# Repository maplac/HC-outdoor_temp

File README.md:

# HC-outdoor_temp

Nahrání bootloaderu do mikrokontroléru:
1. Do Arduino UNO nahrát ArduinoISP sketch.
2. Signálové a napájecí vodiče propojit, jak je uvedeno v https://www.arduino.cc/en/Tutorial/ArduinoToBreadboard a https://github.com/maplac/HC-outdoor_temp/blob/master/bootloader_connection.jpg.
3. Do Arduino IDE přidat MiniCore https://github.com/MCUdude/MiniCore.
4. Nastavit MiniCore - Board:Atmega328, Bootloader:yes, Variant:328P/328PA, BOD:1,8v, Clock:1 MHz internal, Compiler LTO:Disabled. https://github.com/maplac/HC-outdoor_temp/blob/master/bootloader_ide_settings.jpg
5. Nastavit programátor na "Arduino as ISP" a spustit Burn Bootloader.

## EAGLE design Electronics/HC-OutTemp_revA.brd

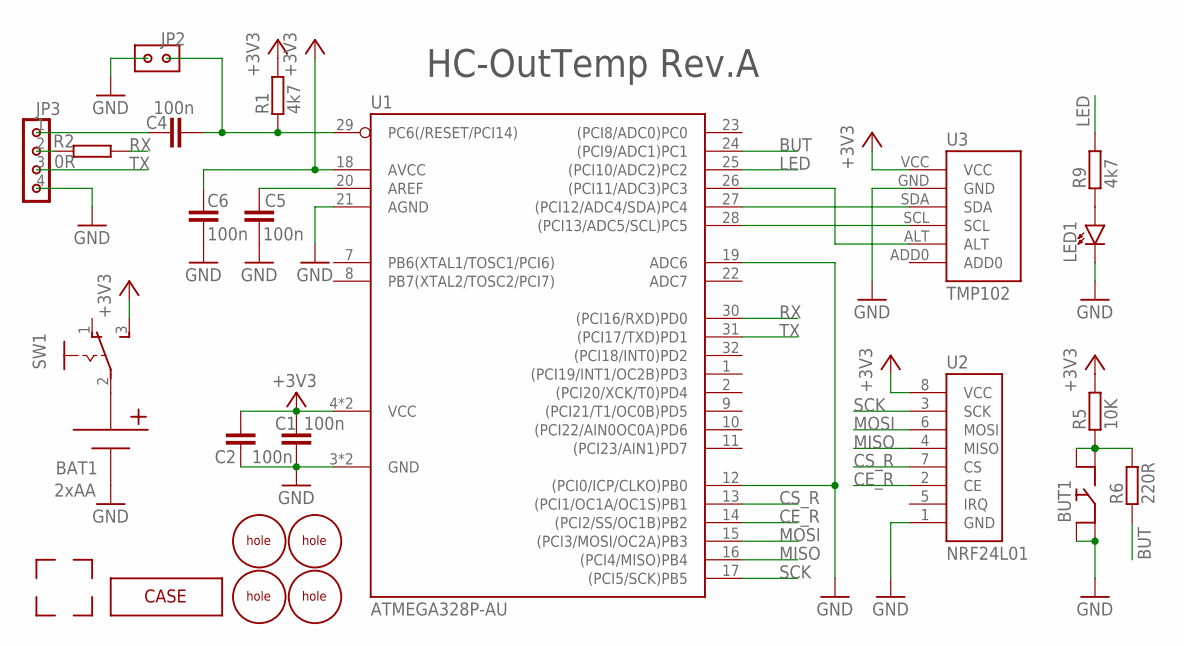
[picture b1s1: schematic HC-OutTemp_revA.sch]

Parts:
BAT1: 2xAA; 2XAA_BATTERY_HOLDER
BUT1: BUTTON'THT'; BUTTON
C1, C2, C4, C5, C6: 100n; C0805
JP2: PINHD2X1; PINHD-2X1
JP3: PINHD3X1; PINHD-4X1-90
LED1: LED'3MM'; LED3MM
R1, R9: 4k7; R0805
R2: 0R; R0805
R5: 10K; R0805
R6: 220R; R0805
SW1: SWITCH_SLIDE; SLIDE_SWITCH
U1: ATMEGA328P-AU; QFP80P900X900X120-32N
U2: NRF24L01
U3: TMP102
U$1, U$2, U$3, U$4: CORNER
U$5, U$6, U$7, U$8: HOLE
U$9: CASE'120X80X40'; CASE-120X80X40

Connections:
+3V3: C1.2, C2.2, C6.2, R1.2, R5.2, SW1.3 (S), U1.4 (VCC), U1.6 (VCC), U1.18 (AVCC), U2.8 (VCC), U3.VCC
BUT: R6.1, U1.24 ((PCI9/ADC1)PC1)
CE_R: U1.14 ((PCI2/SS/OC1B)PB2), U2.2 (CE)
CS_R: U1.13 ((PCI1/OC1A/OC1S)PB1), U2.7 (CS)
GND: BAT1.N, BUT1.2, BUT1.4, C1.1, C2.1, C5.2, C6.1, JP2.1, JP3.4, LED1.K, U1.3 (GND), U1.5 (GND), U1.12 ((PCI0/ICP/CLKO)PB0), U1.19 (ADC6), U1.21 (AGND), U2.1 (GND), U3.GND
LED: R9.2, U1.25 ((PCI10/ADC2)PC2)
MISO: U1.16 ((PCI4/MISO)PB4), U2.4 (MISO)
MOSI: U1.15 ((PCI3/MOSI/OC2A)PB3), U2.6 (MOSI)
unnamed: BAT1.P, SW1.2 (MIDDLE)
unnamed: C4.1, JP2.2, R1.1, U1.29 (PC6(/RESET/PCI14))
unnamed: LED1.A, R9.1
unnamed: U1.26 ((PCI11/ADC3)PC3), U3.ALT
unnamed: C5.1, U1.20 (AREF)
unnamed: C4.2, JP3.1
unnamed: BUT1.1, BUT1.3, R5.1, R6.2
unnamed: JP3.2, R2.2
unnamed: U1.27 ((PCI12/ADC4/SDA)PC4), U3.SDA
unnamed: U1.28 ((PCI13/ADC5/SCL)PC5), U3.SCL
RX: R2.1, U1.30 ((PCI16/RXD)PD0)
SCK: U1.17 ((PCI5/SCK)PB5), U2.3 (SCK)
TX: JP3.3, U1.31 ((PCI17/TXD)PD1)

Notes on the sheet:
HC-OutTemp Rev.A

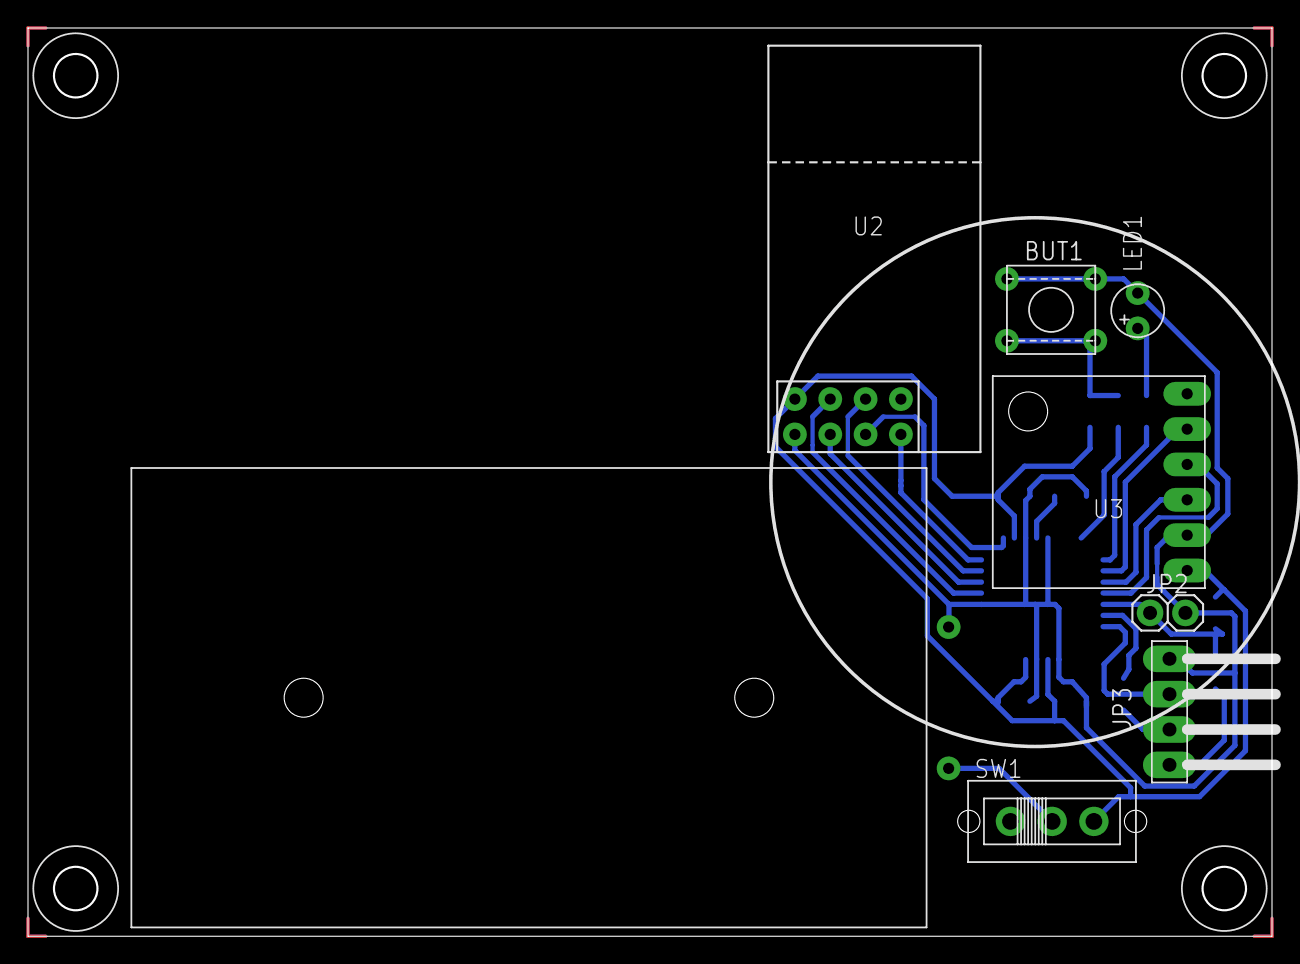
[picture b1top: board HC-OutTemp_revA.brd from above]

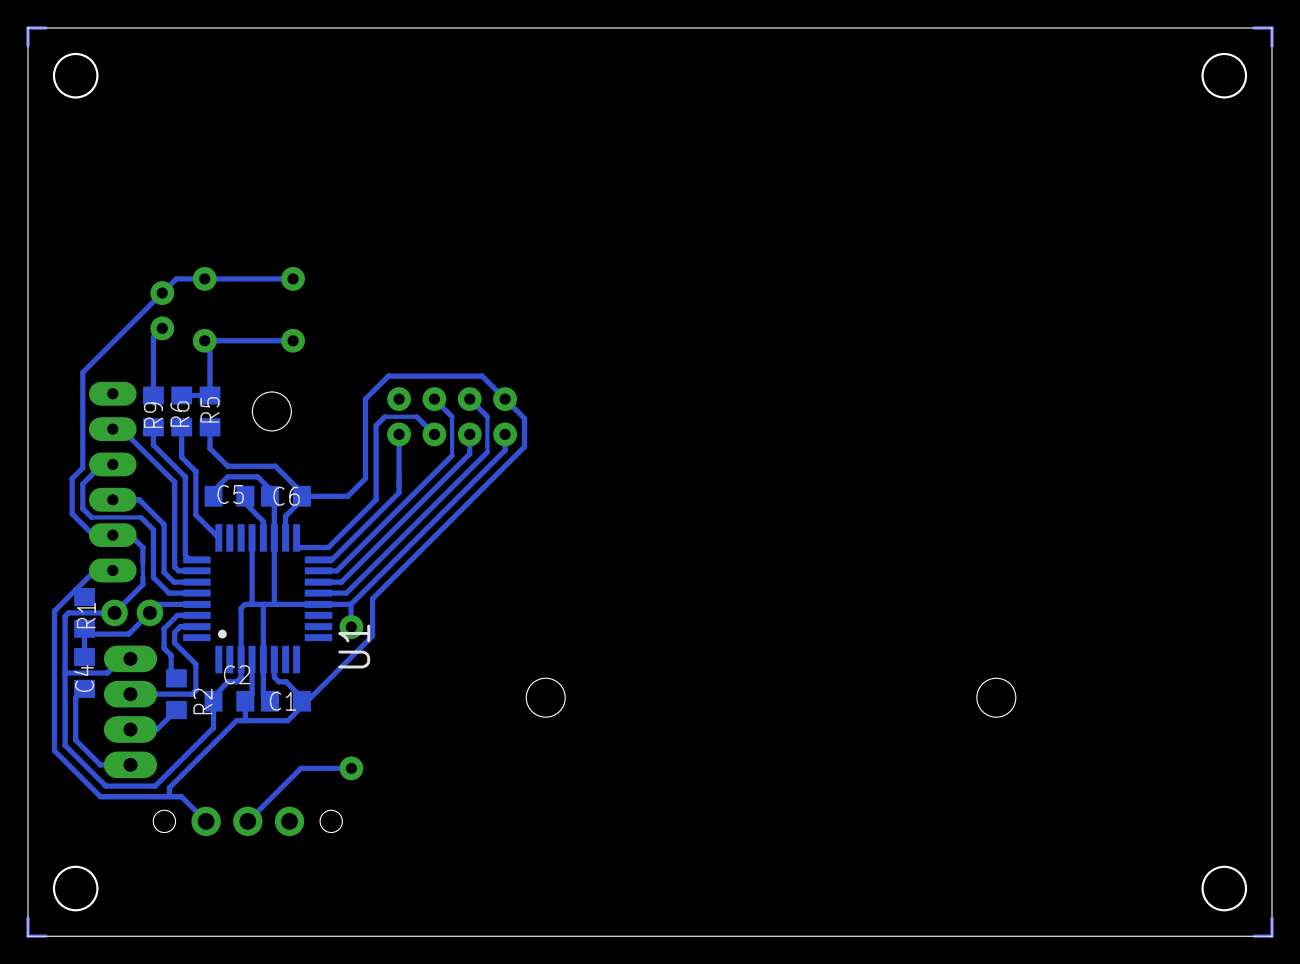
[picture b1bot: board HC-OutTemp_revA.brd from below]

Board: 2 copper layers, 89.4 x 65.3 mm, 28 parts (11 on the bottom side), 21 nets.

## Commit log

2018-02-11 added: circuit diagram
2018-02-11 added: firmware source code
2018-02-11 added: firmware libraries
2018-02-17 changed: firmware - temperature reading and data transfer
2018-02-18 modified: firmware
2018-05-20 added: libraries for reading sensor TMP102 and for reading power supply voltage
2018-05-25 changed: PCB
2018-05-31 changed: MCU package to SMD
2018-06-02 modified: PCB
2018-06-07 added: exported files for PCB manufacturing
2018-06-11 added: pictures of finished and populated PCB
2018-06-11 added: instructions for uploading the bootloader
2018-06-11 modified: README.md - added links to pictures
2018-06-12 modified: the LED blinks twice if the transmission fails
